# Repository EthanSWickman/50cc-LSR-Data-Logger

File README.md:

# 50CC LSR Data Logger 

This repository is the home of data logger development for the 50cc Land Speed Record Motorcycle Racing Team at Oregon State University .

## Compile Instructions (requires Pico SDK) 
- Navigate to /project/build
- Run _cmake ./../_

## Project Structure 
- /project/ - code base (C and CMake) - loosely follows https://cliutils.gitlab.io/modern-cmake/chapters/basics/structure.html
    - /project/apps - files to be compiled into executables
    - /project/src - library implementation files
    - /project/include - library header files
    - /project/build - build directory, contains binaries
    - /project/scripts - build/deploy scripts
    - /project/docs - documentation
    - /project/docs/schematic/ - wiring schematics 
- /examples/ - example cmake projects that exhibit important features of cmake and pico programming in C
- /notes/ - important notes for the datalogging team to reference

## Git Etiquette
- make a branch for new development, keep master clean, compileable, and in sync with the latest wiring diagram
- make targeted commits with meaningful messages

## Attributions
- uses carlk3's SD card interface library: https://github.com/carlk3/no-OS-FatFS-SD-SPI-RPi-Pico (following https://www.digikey.com/en/maker/projects/raspberry-pi-pico-rp2040-sd-card-example-with-micropython-and-cc/e472c7f578734bfd96d437e68e670050)

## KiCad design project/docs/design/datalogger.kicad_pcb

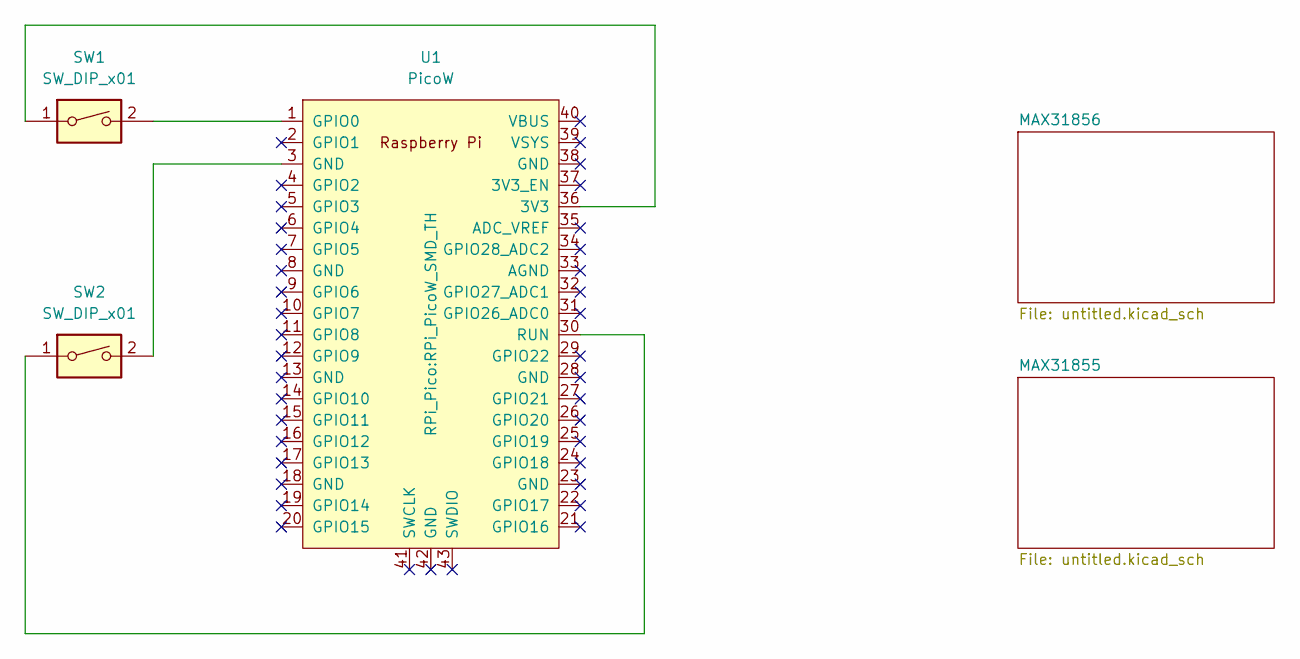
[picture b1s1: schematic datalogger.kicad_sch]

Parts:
SW1, SW2: SW_DIP_x01
U1: PicoW; RPi_PicoW_SMD_TH

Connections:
unnamed: SW1.1, U1.36 (3V3)
unnamed: SW1.2, U1.1 (GPIO0)
unnamed: SW2.1, U1.30 (RUN)
unnamed: SW2.2, U1.3 (GND)

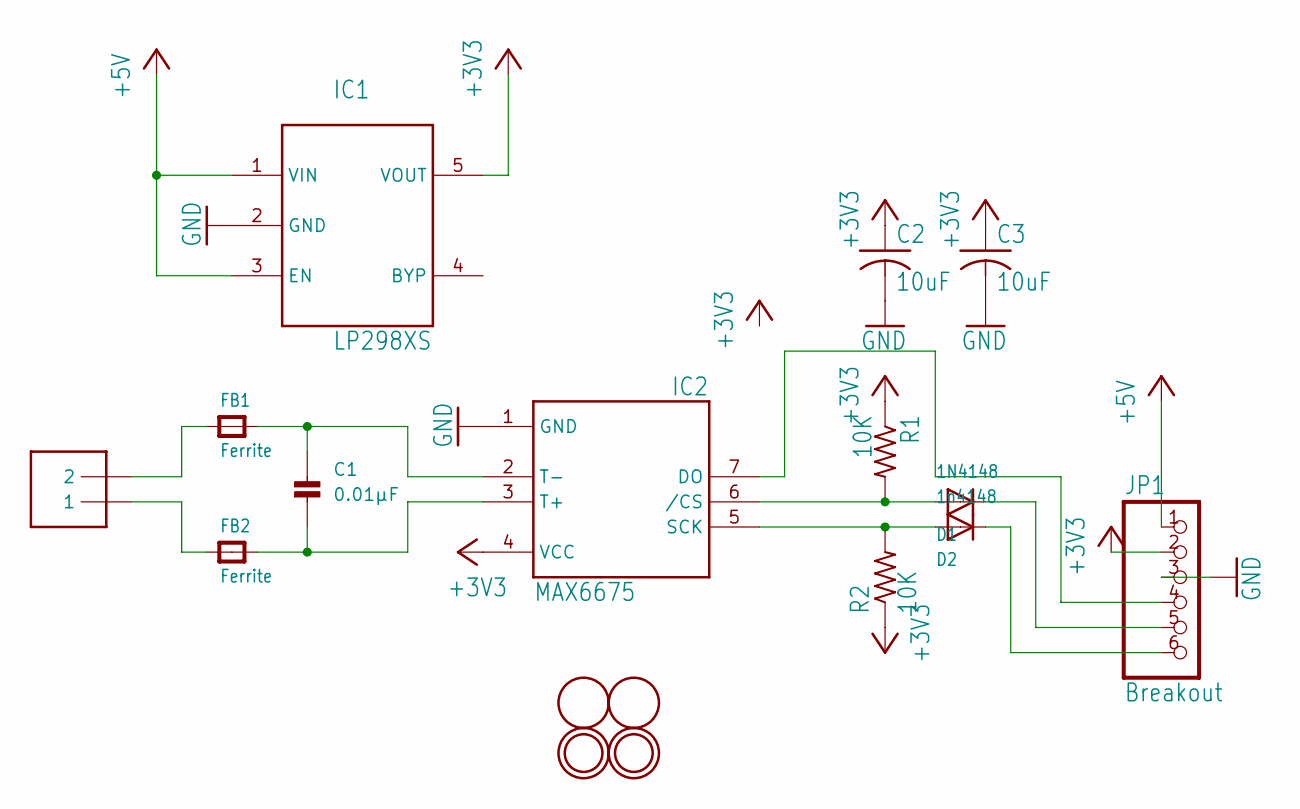
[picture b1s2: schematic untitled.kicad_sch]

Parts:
C1: 0.01µF; _0805
C2, C3: 10uF; C0805K
D1: 1N4148; SOD-323F
D2: 1n4148; SOD-323F
FB1, FB2: Ferrite; _0805
IC1: LP298XS; SOT23-5L
IC2: MAX6675; SO08
J1: 1X2-3.5MM
JP1: Breakout; 1X06_ROUND_76
R1, R2: 10K; R0805
U$1, U$3: FIDUCIAL; FIDUCIAL_1MM
U$2, U$4: MOUNTINGHOLE2.0; MOUNTINGHOLE_2.0_PLATED

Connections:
+3V3: C2.1, C3.1, IC1.5 (VOUT), IC2.4 (VCC), JP1.2, R1.1, R2.1
+5V: IC1.1 (VIN), IC1.3 (EN), JP1.1
GND: C2.2, C3.2, IC1.2 (GND), IC2.1 (GND), JP1.3
unnamed: C1.1, FB1.2, IC2.2 (T-)
unnamed: C1.2, FB2.2, IC2.3 (T+)
unnamed: D1.C, JP1.5
unnamed: D2.C, JP1.6
unnamed: FB1.1, J1.2
unnamed: FB2.1, J1.1
unnamed: IC2.7 (DO), JP1.4
unnamed: D2.A, IC2.5 (SCK), R2.2
unnamed: D1.A, IC2.6 (/CS), R1.2

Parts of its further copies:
U$5: MOUNTINGHOLE2.0; MOUNTINGHOLE_2.0_PLATED

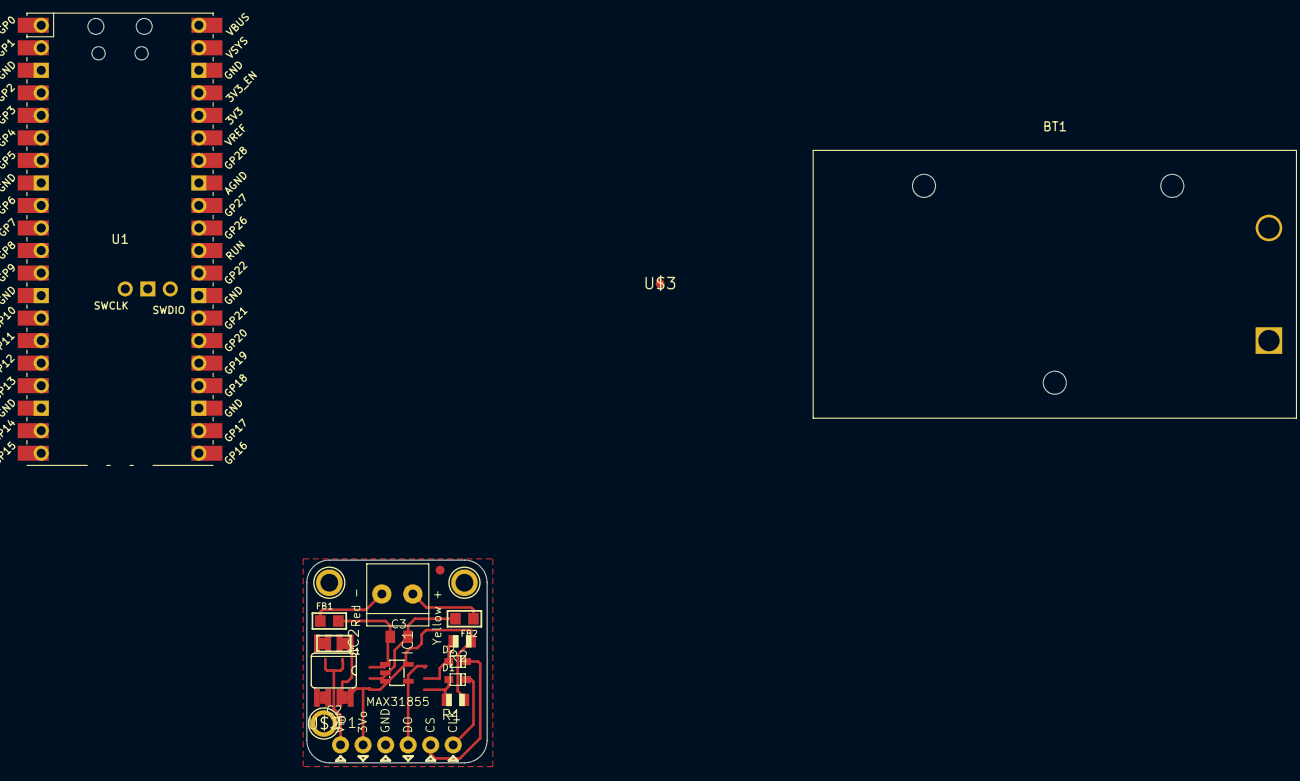
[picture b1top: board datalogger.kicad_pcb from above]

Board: 2 copper layers, 20.3 x 22.9 mm, 21 parts (1 on the bottom side), 12 nets.

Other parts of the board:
BT1: Battery; BatteryHolder_Eagle_12BH611-GR
U$6: ADAFRUIT_3.5MM

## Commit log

2023-10-20 add readme
2023-10-20 add build directory to gitignore
2023-10-20 add sdk to gitignore
2023-10-20 add logger requirements file
2023-10-20 add vscode dotfiles to gitignore
2023-10-20 add basic cmake project template
2023-10-20 add example program using adc and pwm
2023-10-21 add lightshow project to examples
2023-10-21 add basic source project template
2023-10-21 remove build base directories from gitignore
2023-10-21 remove basic build directories from gitignore
2023-10-21 update logger requirements
2023-11-05 add makefile to ignore list
2023-11-06 add basic wiring schematic
2023-11-06 add wiring color to schematic
2023-11-06 add thermocouple boards to schematic'
2023-11-06 add comments to schematic file
2023-11-06 added notes for windows compilation
2023-11-06 update gitignore
2023-11-06 update schematic to use correct GPIOs
2023-11-10 inital outline code for hall effect sensor
2023-11-12 add clock interface code
2023-11-12 alter directory structure
2023-11-12 added clock library and reorganized directory structure
2023-11-12 add ethan's todo to gitignore
2023-11-12 added gitignore
2023-11-12 working velocity sensor prototype
2023-11-12 removed uneeded else
2023-11-12 reorganize cmake structure and add auto-flash script for Ethan's use
2023-11-12 add automatic minicom open to install script
2023-11-12 finished clock implementation and added it to main logging loop
2023-11-12 update project structure in readme
2023-11-12 add prefix to cowbell clock files
2023-11-12 add prefix to pcf8520 clock to associate cowbell
2023-11-13 rename variables
2023-11-13 add sd card library submodule
2023-11-14 pausing for checkout
2023-11-14 test commit
2023-11-14 Made led indicator keep led on constantly. Changed makelists.txt to work with it.
2023-11-14 added gittrack
2023-11-14 set up lcd_directory for work
2023-11-14 added hardware configuration, should be working now
2023-11-17 add completed sd card implemantation
2023-11-17 moved pico sd card interface library
2023-11-17 finish basic sd card implementation
2023-11-18 add progress to cloud
2023-11-23 add multicore logging, with awful bug that needs to be explored
2023-11-23 one bug fixed, another begins, something is crashing with frequency > 200 hz ish
2023-11-28 finish sd card writing w/ multicores up to 50hz logs
2023-11-28 remove external sd card library (will put back in a moment)
2023-11-28 re-adding pico sd card library
2023-11-28 add writebuffer documentation
2023-11-28 remove old time struct
2023-11-29 hopefully added thermos w/ csn to logger
2023-11-30 add global pin configuration file
2023-12-19 functionized code and adopted pin config
2023-12-19 inital commit
2023-12-20 start kicad diagram
2023-12-20 cowbell working
2023-12-20 commented code and fixed thermo math
2023-12-20 refactored new code
2023-12-20 moved alarm test version to different .c file
2023-12-21 removed uneeded copy of sd card library
2023-12-21 fixed C to F
2024-01-03 cleaned up pin config file
2024-01-04 clean up main.c
2024-01-04 change full buffer warning message
2024-01-04 clean up pin config file
2024-01-04 remove print calls
2024-01-04 clean up main
2024-01-05 added functionality for multiple thermos configurable with CMAKE file
2024-01-10 finished boilerplate
2024-01-10 fix time
2024-01-10 remove unnecessary functions
2024-01-11 cleanup main
2024-01-22 cleanup finished
2024-01-22 dylan commits (3 thermos)
2024-02-05 added temp? verbosity variables
2024-02-05 changed start logs to 28, other minor things
2024-02-26 Most recent version (30 hz)
2024-03-05 add lcd
2024-03-06 lcd proof of concept
2024-03-15 ready for dylan
2024-04-17 hall effect test
